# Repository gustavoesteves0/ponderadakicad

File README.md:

As pastas estão organizadas da seguinte forma: 

```
|--ponderada_kicad/
|  |--ponderada_kicad-backups/
|  |--fp-info-cache
|  |--ponderada_kicad.kicad_pcb        
|  |--ponderada_kicad.kicad_prl        
|  |--ponderada_kicad.kicad_pro        
|  |--ponderada_kicad.kicad_sch
```     

Obs: a atividade foi realizada em conjunto com o aluno Marco Antonio Rizzi

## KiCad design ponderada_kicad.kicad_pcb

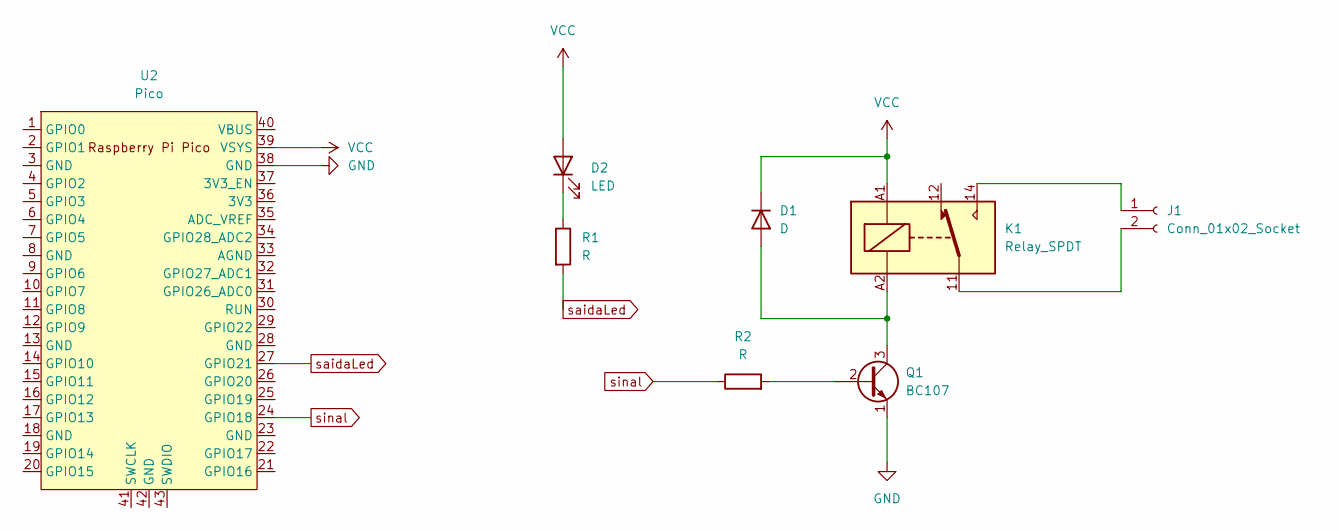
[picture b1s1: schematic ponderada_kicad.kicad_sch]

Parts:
D1: D; D_MELF_Handsoldering
D2: LED; LED_1812_4532Metric
J1: Conn_01x02_Socket; AMASS_XT60-M_1x02_P7.20mm_Vertical
K1: Relay_SPDT; Relay_SPDT_Finder_40.31
Q1: BC107; TO-18-3
R1: R; R_LDR_5.0x4.1mm_P3mm_Vertical
R2: R; R_0603_1608Metric_Pad0.98x0.95mm_HandSolder
U2: Pico; RPi_Pico_SMD_TH

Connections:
GND: Q1.1 (E), U2.38 (GND)
unnamed: D1.2 (A), K1.A2, Q1.3 (C)
unnamed: D2.1 (K), R1.1
unnamed: J1.1, K1.14
unnamed: J1.2, K1.11
unnamed: Q1.2 (B), R2.2
VCC: D1.1 (K), D2.2 (A), K1.A1, U2.39 (VSYS)
saidaLed: R1.2, U2.27 (GPIO21)
sinal: R2.1, U2.24 (GPIO18)

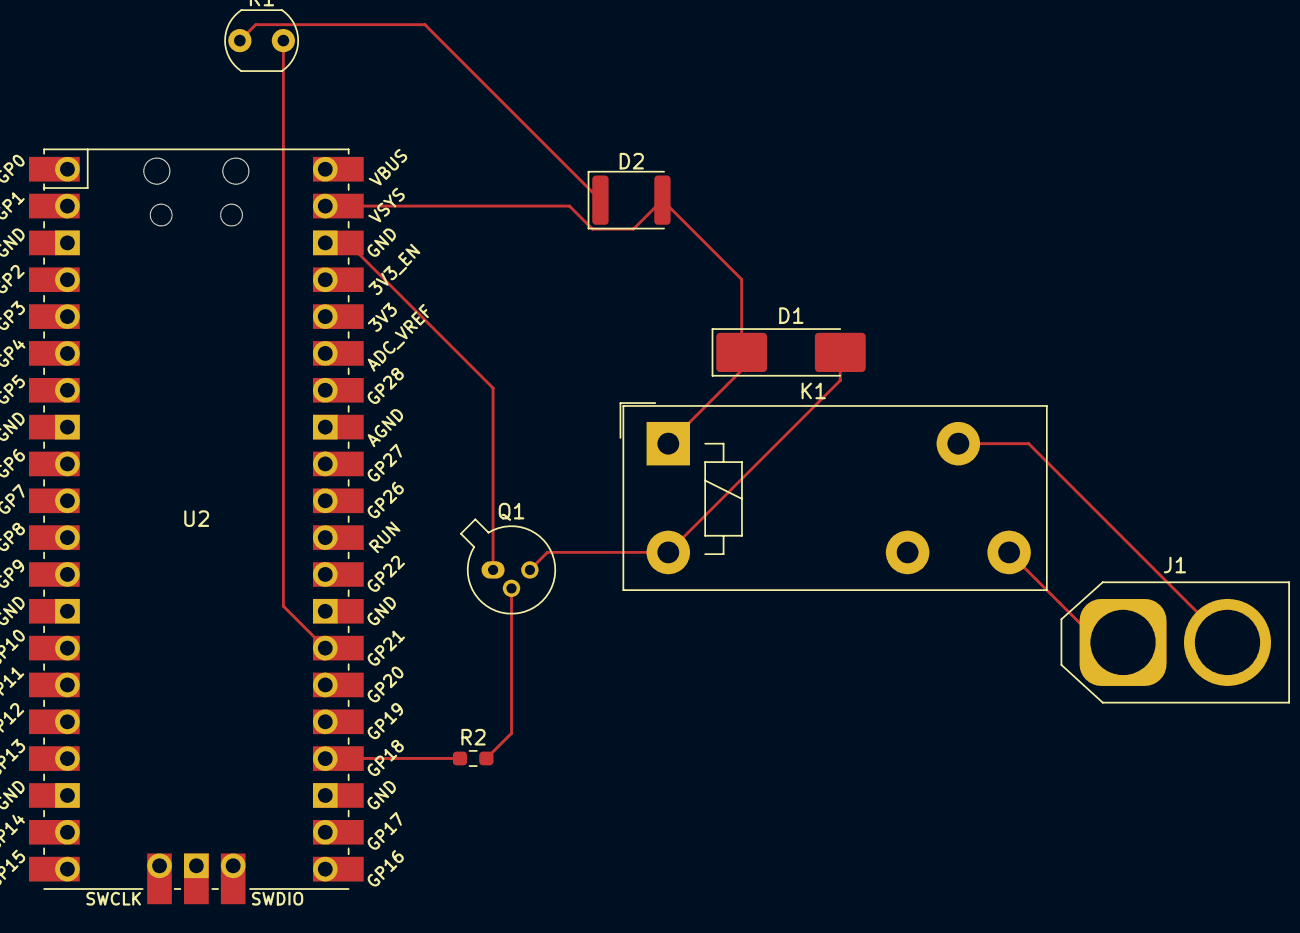
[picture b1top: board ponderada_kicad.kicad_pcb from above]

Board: 2 copper layers, 8 parts (0 on the bottom side), 9 nets.

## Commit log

2024-04-01 adição de créditos ao Rizzi
